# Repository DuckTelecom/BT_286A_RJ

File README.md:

# BT_286A_RJ

This PCB converts the two screw terminals on a BT / Vanderhoff Test Telephone 286A to an RJ11 and RJ45 socket - the idea being you can then use additional adapters like an RJ45 to BT "Master". I have made a vague attempt at impedance and length matching, mostly as an experiment.

Why not just use a standard BT socket I hear you ask? Well, PCB mount BT sockets appear almost impossible to source. I found one supplier but they ignored my emails and phone calls. If you can get hold of them, please get in touch.

The RJ11 and RJ45 connectors were sourced from AliExpress. As a result they don't have part numbers but they're fairly common parts. Hopefully you can identify them from the images - if you're unsure please get in touch.

I had the PCBs manufactured by [JLCPCB](https://jlcpcb.com/). They were able to correctly interpret the pads on the edge of the board and cut the correct shape. I didn't opt for castellated holes due to the additional expense. As a result only the top half of the pad is plated on the board edge but this isn't an issue.

## Images

### Assembled adapter

### Installed adapter

### PCB Front

### PCB Rear

### RJ11 Connector

### RJ45 Connector

## Licence

This project is licensed under the [Creative Commons CC BY-SA 4.0](https://creativecommons.org/licenses/by-sa/4.0/) licence.

You are free to share and adapt the code as required, however you *must* give appropriate credit and indicate what changes have been made. You must also distribute your adaptation under the same license.

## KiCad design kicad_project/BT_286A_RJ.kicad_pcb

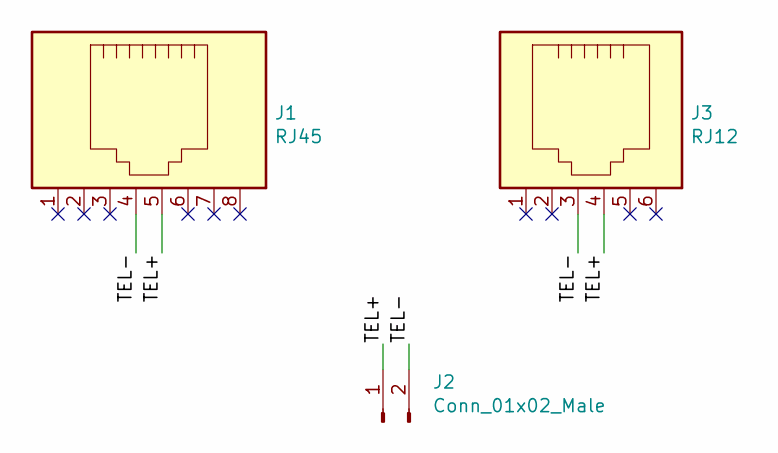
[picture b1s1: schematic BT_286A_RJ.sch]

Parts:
J1: RJ45; AliExpress_Horizontal_RJ45
J2: Conn_01x02_Male; BT_286A_TERMINALS
J3: RJ12; AliExpress_Horizontal_RJ11

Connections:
/TEL+: J1.5, J2.1, J3.4
/TEL-: J1.4, J2.2, J3.3

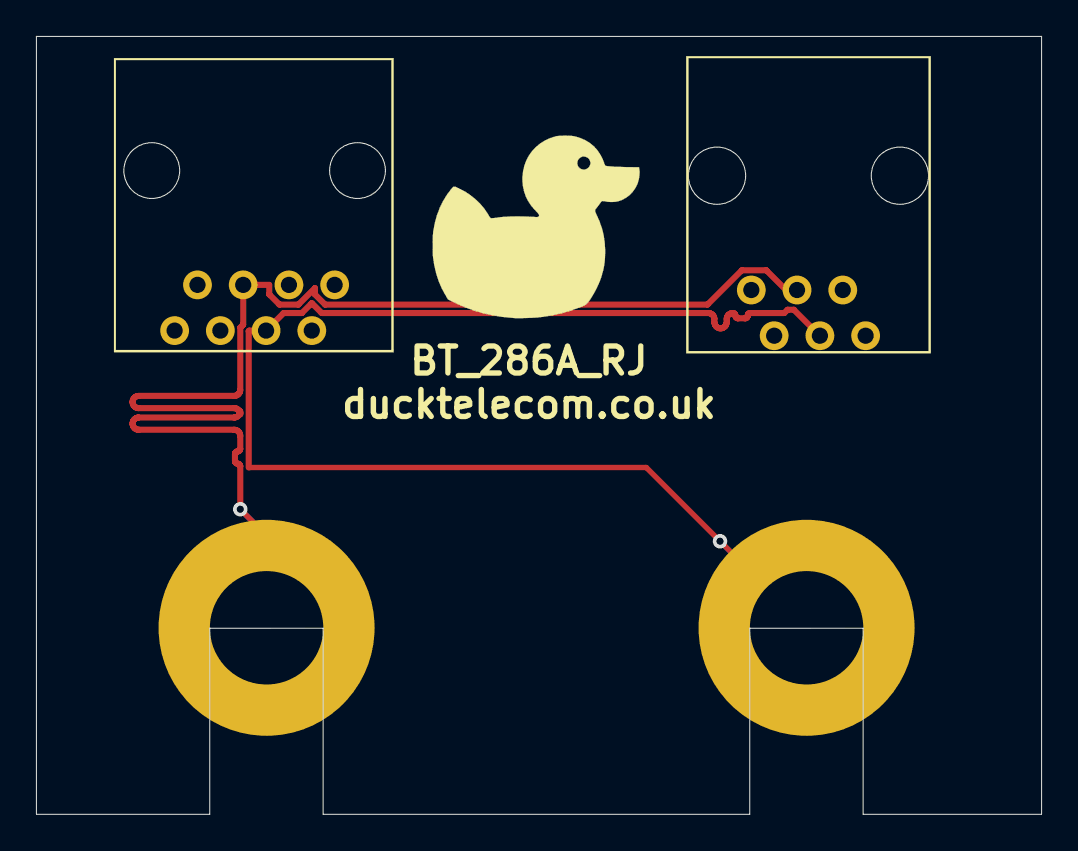
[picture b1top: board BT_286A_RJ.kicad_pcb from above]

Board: 2 copper layers, 55.8 x 43.2 mm, 4 parts (0 on the bottom side), 2 nets.

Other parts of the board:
Ref**: Val**; duck
